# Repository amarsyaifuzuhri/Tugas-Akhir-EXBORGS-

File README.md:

# Tugas-Akhir
halaman ini berisi tentang beberapa desain dari tugas akhir yang saya buat, untuk keperluan penelitian kedepan agar lebih baik maka saya buat open source agar dikembangkan lagi

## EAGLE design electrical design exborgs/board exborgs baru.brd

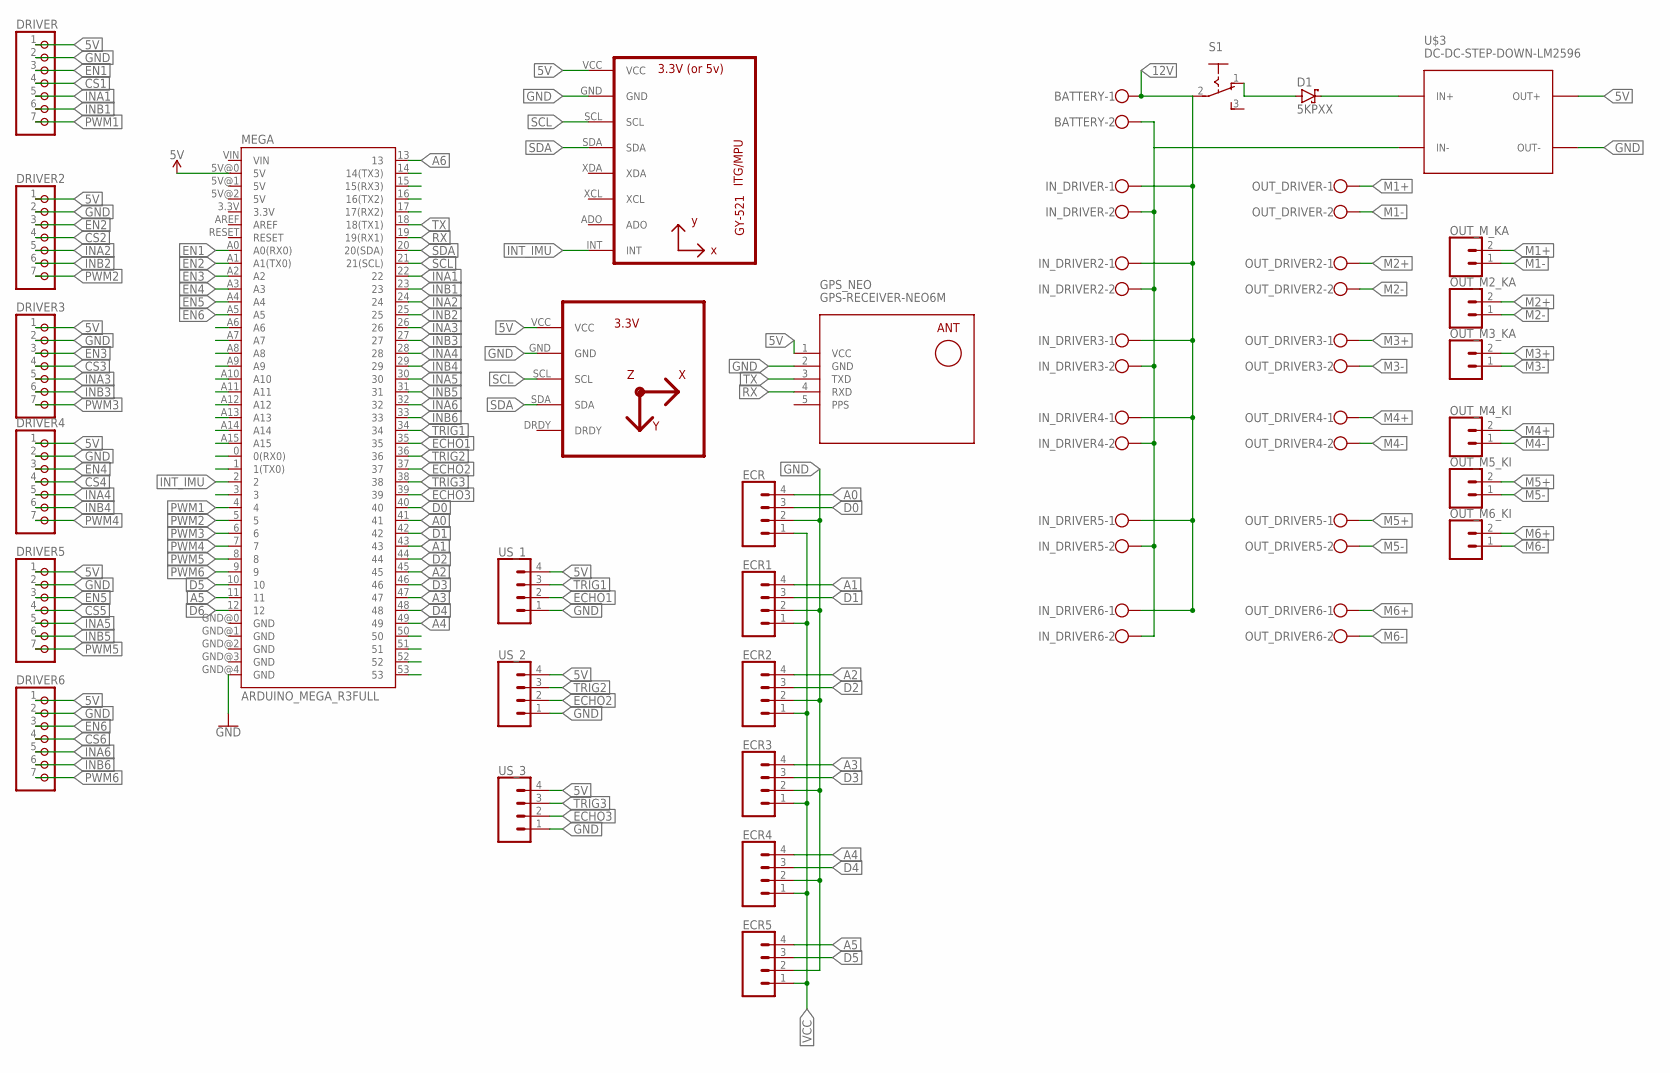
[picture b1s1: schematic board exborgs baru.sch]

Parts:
BATTERY: W237-102
D1: 5KPXX; P6T15
DRIVER, DRIVER2, DRIVER3, DRIVER4, DRIVER5, DRIVER6: PINHD-1X7; 1X07
ECR, ECR1, ECR2, ECR3, ECR4, ECR5: CONN_04POLAR; MOLEX-1X4
GPS_NEO: GPS-RECEIVER-NEO6M
IMU: GY-521MPU6050; GY-521
IN_DRIVER, IN_DRIVER2, IN_DRIVER3, IN_DRIVER4, IN_DRIVER5, IN_DRIVER6: W237-102
KOMPAS: HMC5883LGY-271; GY-271
MEGA: ARDUINO_MEGA_R3FULL; ARDUINO_MEGA
OUT_DRIVER, OUT_DRIVER2, OUT_DRIVER3, OUT_DRIVER4, OUT_DRIVER5, OUT_DRIVER6: W237-102
OUT_M2_KA, OUT_M3_KA, OUT_M4_KI, OUT_M5_KI, OUT_M6_KI: CONN_02POLAR; MOLEX-1X2
OUT_M_KA: CONN_02POLAR; MOLEX-1X2
S1: 255SB
U$3: DC-DC-STEP-DOWN-LM2596
US_1, US_2, US_3: CONN_04POLAR; MOLEX-1X4

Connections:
5V: DRIVER.1, DRIVER2.1, DRIVER3.1, DRIVER4.1, DRIVER5.1, DRIVER6.1, GPS_NEO.1 (VCC), IMU.VCC, KOMPAS.VCC, MEGA.5V@0 (5V), U$3.OUT+, US_1.4, US_2.4, US_3.4
12V: BATTERY.1, IN_DRIVER.1, IN_DRIVER2.1, IN_DRIVER3.1, IN_DRIVER4.1, IN_DRIVER5.1, IN_DRIVER6.1, S1.2
A0: ECR.4, MEGA.41
A1: ECR1.4, MEGA.43
A2: ECR2.4, MEGA.45
A3: ECR3.4, MEGA.47
A4: ECR4.4, MEGA.49
A5: ECR5.4, MEGA.11
A6: MEGA.13
CS1: DRIVER.4
CS2: DRIVER2.4
CS3: DRIVER3.4
CS4: DRIVER4.4
CS5: DRIVER5.4
CS6: DRIVER6.4
D0: ECR.3, MEGA.40
D1: ECR1.3, MEGA.42
D2: ECR2.3, MEGA.44
D3: ECR3.3, MEGA.46
D4: ECR4.3, MEGA.48
D5: ECR5.3, MEGA.10
D6: MEGA.12
ECHO1: MEGA.35, US_1.2
ECHO2: MEGA.37, US_2.2
ECHO3: MEGA.39, US_3.2
EN1: DRIVER.3, MEGA.A0 (A0(RX0))
EN2: DRIVER2.3, MEGA.A1 (A1(TX0))
EN3: DRIVER3.3, MEGA.A2
EN4: DRIVER4.3, MEGA.A3
EN5: DRIVER5.3, MEGA.A4
EN6: DRIVER6.3, MEGA.A5
GND: DRIVER.2, DRIVER2.2, DRIVER3.2, DRIVER4.2, DRIVER5.2, DRIVER6.2, ECR.2, ECR1.2, ECR2.2, ECR3.2, ECR4.2, ECR5.2, GPS_NEO.2 (GND), IMU.GND, KOMPAS.GND, MEGA.GND@4 (GND), U$3.OUT-, US_1.1, US_2.1, US_3.1
INA1: DRIVER.5, MEGA.22
INA2: DRIVER2.5, MEGA.24
INA3: DRIVER3.5, MEGA.26
INA4: DRIVER4.5, MEGA.28
INA5: DRIVER5.5, MEGA.30
INA6: DRIVER6.5, MEGA.32
INB1: DRIVER.6, MEGA.23
INB2: DRIVER2.6, MEGA.25
INB3: DRIVER3.6, MEGA.27
INB4: DRIVER4.6, MEGA.29
INB5: DRIVER5.6, MEGA.31
INB6: DRIVER6.6, MEGA.33
INT_IMU: IMU.INT, MEGA.2
M1+: OUT_DRIVER.1, OUT_M_KA.2
M1-: OUT_DRIVER.2, OUT_M_KA.1
M2+: OUT_DRIVER2.1, OUT_M2_KA.2
M2-: OUT_DRIVER2.2, OUT_M2_KA.1
M3+: OUT_DRIVER3.1, OUT_M3_KA.2
M3-: OUT_DRIVER3.2, OUT_M3_KA.1
M4+: OUT_DRIVER4.1, OUT_M4_KI.2
M4-: OUT_DRIVER4.2, OUT_M4_KI.1
M5+: OUT_DRIVER5.1, OUT_M5_KI.2
M5-: OUT_DRIVER5.2, OUT_M5_KI.1
M6+: OUT_DRIVER6.1, OUT_M6_KI.2
M6-: OUT_DRIVER6.2, OUT_M6_KI.1
unnamed: D1.A, S1.1 (O)
unnamed: D1.C, U$3.IN+
unnamed: BATTERY.2, IN_DRIVER.2, IN_DRIVER2.2, IN_DRIVER3.2, IN_DRIVER4.2, IN_DRIVER5.2, IN_DRIVER6.2, U$3.IN-
PPS: GPS_NEO.5 (PPS)
PWM1: DRIVER.7, MEGA.4
PWM2: DRIVER2.7, MEGA.5
PWM3: DRIVER3.7, MEGA.6
PWM4: DRIVER4.7, MEGA.7
PWM5: DRIVER5.7, MEGA.8
PWM6: DRIVER6.7, MEGA.9
RX: GPS_NEO.4 (RXD), MEGA.19 (19(RX1))
SCL: IMU.SCL, KOMPAS.SCL, MEGA.21 (21(SCL))
SDA: IMU.SDA, KOMPAS.SDA, MEGA.20 (20(SDA))
TRIG1: MEGA.34, US_1.3
TRIG2: MEGA.36, US_2.3
TRIG3: MEGA.38, US_3.3
TX: GPS_NEO.3 (TXD), MEGA.18 (18(TX1))
VCC: ECR.1, ECR1.1, ECR2.1, ECR3.1, ECR4.1, ECR5.1

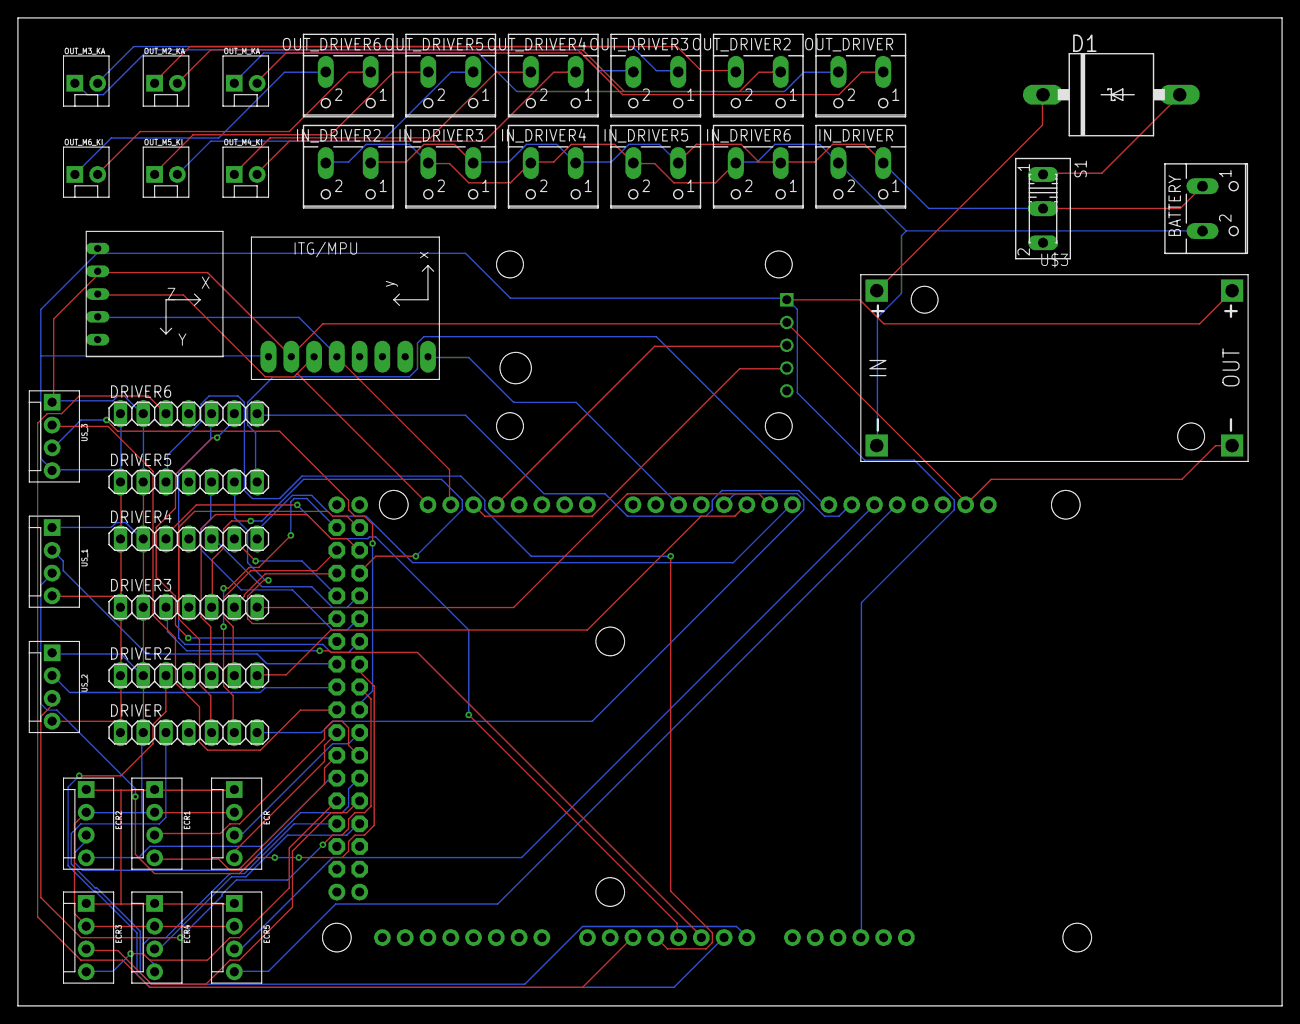
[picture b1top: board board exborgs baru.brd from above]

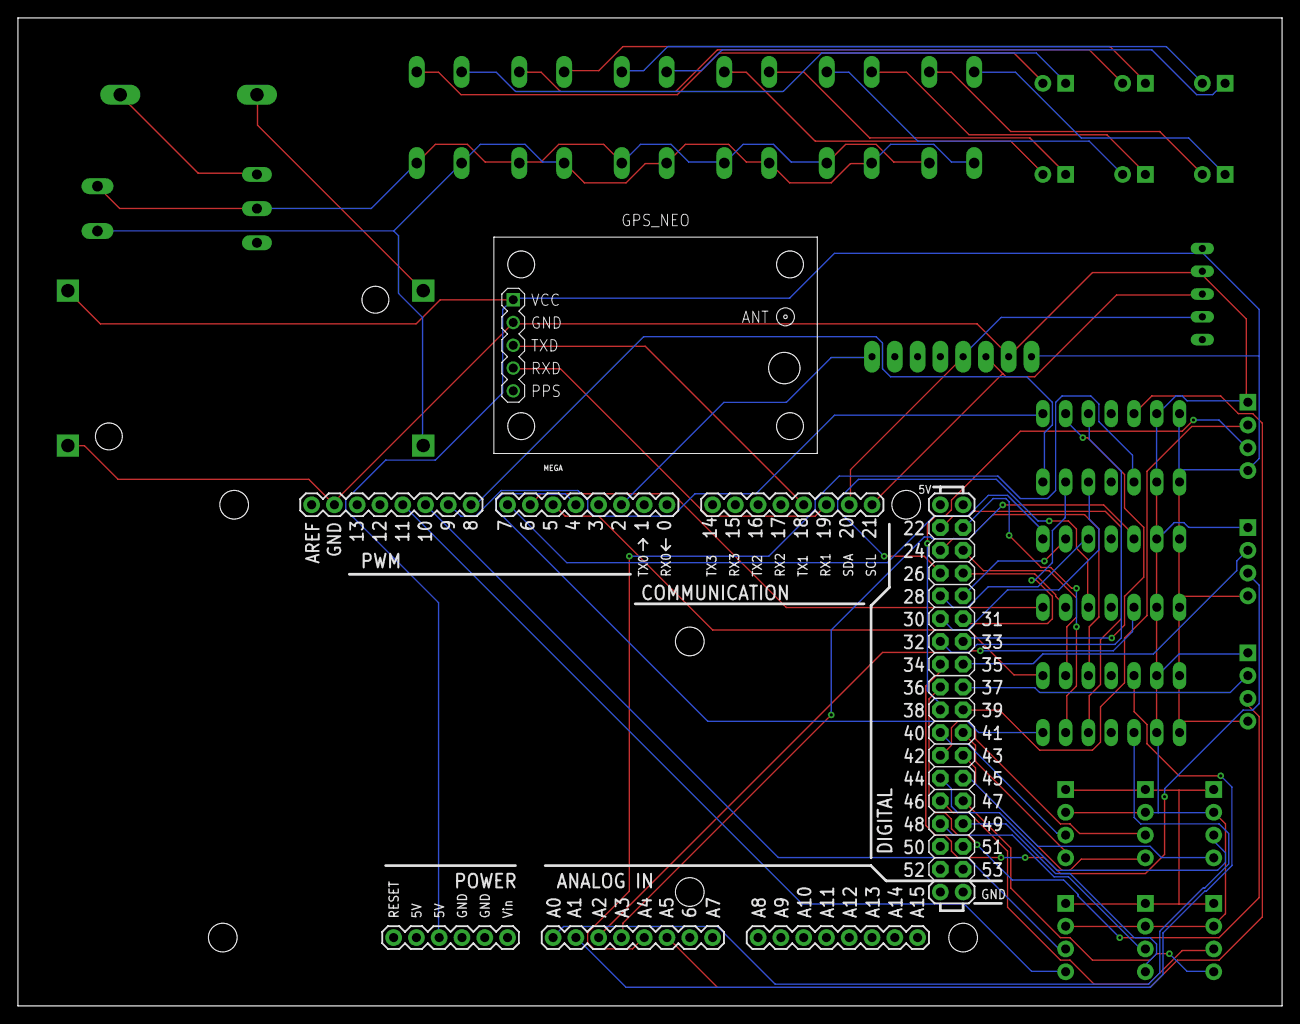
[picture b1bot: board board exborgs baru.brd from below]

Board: 2 copper layers, 141.0 x 110.2 mm, 41 parts (2 on the bottom side), 66 nets.

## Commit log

2020-08-07 Create source code

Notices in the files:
parts and their libraries:
SparkFun-Connectors: Licensing: Creative Commons ShareAlike 4.0 International - https://creativecommons.org/licenses/by-sa/4.0
diy-modules: Released under the Creative Commons Attribution 4.0 International License: http://creativecommons.org/licenses/by/4.0
